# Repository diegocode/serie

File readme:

Recursos para la utilización del puerto serie 
en entornos GNU/Linux

Conjunto de recursos para aprendizaje y trabajo con el puerto serie

- Material de referencia (Hardware, y software en Python + PySerial)

- Ejemplos (Python, Qt y C++)

- Aplicaciones:
  
  sloopback - para diagnóstico
  
  dcterm - terminal con capacidad de registrador y de enviar datos 
  
  controldig - control y monitoreo digital usando las líneas de 
               handshaking pensado para su utilización por personas 
               sin conocimientos de programación. 
               
  dig_es: GUI de controldig

-----------------------------------------------------------------------
estructura del respositorio
-----------------------------------------------------------------------
.
├── controldig
│   ├── docs
│   └── hardware
├── dcterm
│   └── docs
├── referencia
│   ├── ejemplos
│   │   └── clima
│   │       └── arduino
│   └── Qt + Cpp
├── serie-web
│   ├── clima
│   ├── files
│   ├── img
│   └── video
└── sloopback
    └── docs

17 directories

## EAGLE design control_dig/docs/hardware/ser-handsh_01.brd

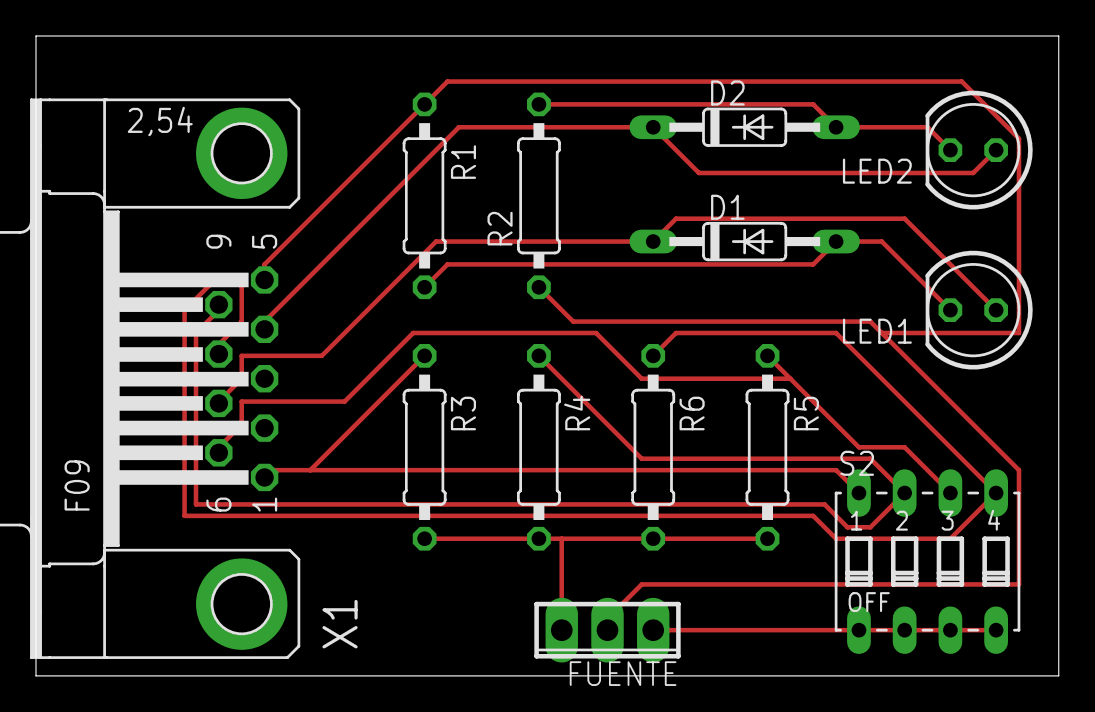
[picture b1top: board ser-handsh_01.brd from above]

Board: 1 copper layer, 56.8 x 35.5 mm, 13 parts (0 on the bottom side), 11 nets.

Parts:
D1, D2: 1N4148DO35-10; DO35-10
FUENTE: 3POL254
LED1, LED2: LED5MM
R1, R2, R3, R4, R5, R6: 0207/10
S2: DIP04S
X1: F09HP

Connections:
+12V: FUENTE.1, S2.1, S2.2, S2.3, S2.4
-12V: FUENTE.3, R3.2, R4.2, R5.2, R6.2
CTS: R6.1, S2.5, X1.8
DCD: R3.1, S2.8, X1.1
DSR: R5.1, S2.6, X1.6
DTR: D2.C, LED2.A, X1.4
GND: FUENTE.2, R1.1, R2.1, X1.5
unnamed: D1.A, LED1.K, R1.2
unnamed: D2.A, LED2.K, R2.2
RI: R4.1, S2.7, X1.9
RTS: D1.C, LED1.A, X1.7

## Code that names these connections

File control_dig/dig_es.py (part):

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        self.bmpRI = wx.StaticBitmap(self.panel_2, wx.ID_ANY, wx.Bitmap("off.png", wx.BITMAP_TYPE_ANY))
        self.label_2 = wx.StaticText(self.panel_2, wx.ID_ANY, _("RI"))
        self.bmpDSR = wx.StaticBitmap(self.panel_2, wx.ID_ANY, wx.Bitmap("off.png", wx.BITMAP_TYPE_ANY))
        self.label_3 = wx.StaticText(self.panel_2, wx.ID_ANY, _("DSR\n"))
        self.bmpCTS = wx.StaticBitmap(self.panel_2, wx.ID_ANY, wx.Bitmap("on.png", wx.BITMAP_TYPE_ANY))
        self.label_4 = wx.StaticText(self.panel_2, wx.ID_ANY, _("CTS\n"))
        self.sizer_5_staticbox = wx.StaticBox(self.panel_2, wx.ID_ANY, _("entradas"))
        self.panel_3 = wx.Panel(self.panel_1, wx.ID_ANY)
        self.bmpDTR = wx.StaticBitmap(self.panel_3, wx.ID_ANY, wx.Bitmap("on.png", wx.BITMAP_TYPE_ANY))
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    def hbtnDTR(self, event):  # wxGlade: mainUI.<event_handler>
        
        if controldig.ser.dtr:
            controldig.ser.dtr = 0
            self.bmpDTR.SetBitmap(wx.BitmapFromImage(self.imgOff))
            self.btnDTR.SetLabel("DTR set")
        else:
            controldig.ser.dtr = 1
            self.bmpDTR.SetBitmap(wx.BitmapFromImage(self.imgOn))
            self.btnDTR.SetLabel("DTR reset")               

    def hbtnRTS(self, event):  # wxGlade: mainUI.<event_handler>
        if controldig.ser.rts:
            controldig.ser.rts = 0
            #img = wx.Image("off.png", wx.BITMAP_TYPE_ANY)
            self.bmpRTS.SetBitmap(wx.BitmapFromImage(self.imgOff))
            self.btnRTS.SetLabel("RTS set")
        else:
            controldig.ser.rts = 1
            #img = wx.Image("on.png", wx.BITMAP_TYPE_ANY)
            self.bmpRTS.SetBitmap(wx.BitmapFromImage(self.imgOn))
            self.btnRTS.SetLabel("RTS reset")
        
        
    def hbtnScriptLoad(self, event):  # wxGlade: mainUI.<event_handler>
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        event.Skip()

    def actualizaEstado(self, p, pin):
        if pin == 1: # DCD
            if p.cd:
                self.bmpCD.SetBitmap(wx.BitmapFromImage(self.imgOn))
            else:
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            else:
                self.bmpRI.SetBitmap(wx.BitmapFromImage(self.imgOff))            

        if pin == 8: # CTS
            if p.cts:
                self.bmpCTS.SetBitmap(wx.BitmapFromImage(self.imgOn))
            else:
                self.bmpCTS.SetBitmap(wx.BitmapFromImage(self.imgOff))
                
        if pin == 6: # DSR
            if p.dsr:
                self.bmpDSR.SetBitmap(wx.BitmapFromImage(self.imgOn))
            else:
                self.bmpDSR.SetBitmap(wx.BitmapFromImage(self.imgOff))
     
        if pin == 4: # DTR
            if p.dtr:
                self.bmpDTR.SetBitmap(wx.BitmapFromImage(self.imgOn))
                self.btnDTR.SetLabel("DTR reset") 
            else:
                self.bmpDTR.SetBitmap(wx.BitmapFromImage(self.imgOff))    
                self.btnDTR.SetLabel("DTR set") 

        if pin == 7: # RTS
            if p.rts:
                self.bmpRTS.SetBitmap(wx.BitmapFromImage(self.imgOn))
                self.btnRTS.SetLabel("RTS reset") 
            else:
                self.bmpRTS.SetBitmap(wx.BitmapFromImage(self.imgOff))   
                self.btnRTS.SetLabel("RTS set") 
            
def timeout_scan( s, estados, c, log ):    
    """se ejecuta cada t_scan"""
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
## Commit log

2016-01-23 primer esbozo de loopback
2016-01-27 control digital funcional linea comandos
2016-01-27 control_dig nombres custom
2016-01-27 docs folder
2016-01-30 scripts+config+docs
2016-01-30 con clase timer propia + ctrl-c correcto
2016-01-30 con clase timer propia + ctrl-c correcto - Timer-daemon=True
2016-01-30 log funcionando - con configuración
2016-02-05 terminal base + adquisición de datos y site ajax + inicio referencia
2016-02-11 referencia y loopback ok + ejemplo Qt y Cpp
2016-02-12 gui control_dig
2016-02-14 documentación corregida + orden fuentes
2016-02-14 reorganización y documentación mejorada
2016-02-15 agregada la licencia en todos los fuentes
2016-02-19 dcterm modificado - ahora funciona casi todo!-a
2016-02-19 sin archivos irrelevantes
2016-02-19 agregado site de presentacion del materia
2016-02-20 dcterm: exception en requests
2018-08-30 Agrego Licencia
2018-11-11 Rename dcterm.txt to sloopback.txt
